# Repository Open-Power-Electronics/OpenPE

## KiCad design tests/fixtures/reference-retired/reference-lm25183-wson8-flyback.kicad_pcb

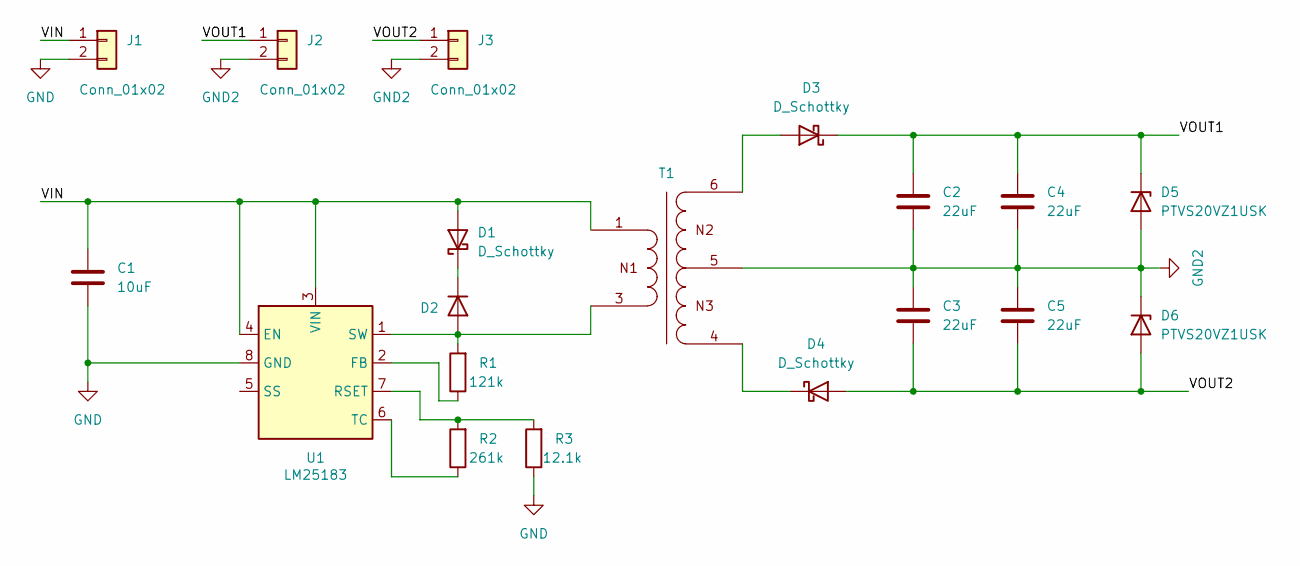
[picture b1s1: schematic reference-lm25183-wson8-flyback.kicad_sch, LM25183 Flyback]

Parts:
C1: 10uF; C_1210_3225Metric
C2, C3, C4, C5: 22uF; C_1210_3225Metric
D1: D_Schottky; D_SMA
D2: D_SOD-123F
D3, D4: D_Schottky; D_PowerDI-123
D5, D6: PTVS20VZ1USK; Nexperia_CFP3_SOD-123W
J1, J2, J3: Conn_01x02; PhoenixContact_GMSTBA_2,5_2-G-7,62_1x02_P7.62mm_Horizontal
R1: 121k; R_0402_1005Metric
R2: 261k; R_0402_1005Metric
R3: 12.1k; R_0402_1005Metric
T1: EP7_5801_750344600; T_Wurth_WE-FLYTI-EP7_5801; Part Number 750344600
U1: LM25183; WSON-8-1EP_4x4mm_P0.8mm_EP2.2x3mm

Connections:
/VIN: C1.1, D1.2 (A), J1.1, T1.1, U1.3 (VIN), U1.4 (EN)
/VOUT1: C2.1, C4.1, D3.1 (K), D5.1 (K), J2.1
/VOUT2: C3.2, C5.2, D4.2 (A), D6.2 (A), J3.1
GND: C1.2, J1.2, R3.1, U1.8 (GND)
GND2: C2.2, C3.1, C4.2, C5.1, D5.2 (A), D6.1 (K), J2.2, J3.2, T1.5
unnamed: D1.1 (K), D2.1 (K)
unnamed: D2.2 (A), R1.2, T1.3, U1.1 (SW)
unnamed: D3.2 (A), T1.6
unnamed: D4.1 (K), T1.4
unnamed: R1.1, U1.2 (FB)
unnamed: R2.2, R3.2, U1.7 (RSET)
unnamed: R2.1, U1.6 (TC)

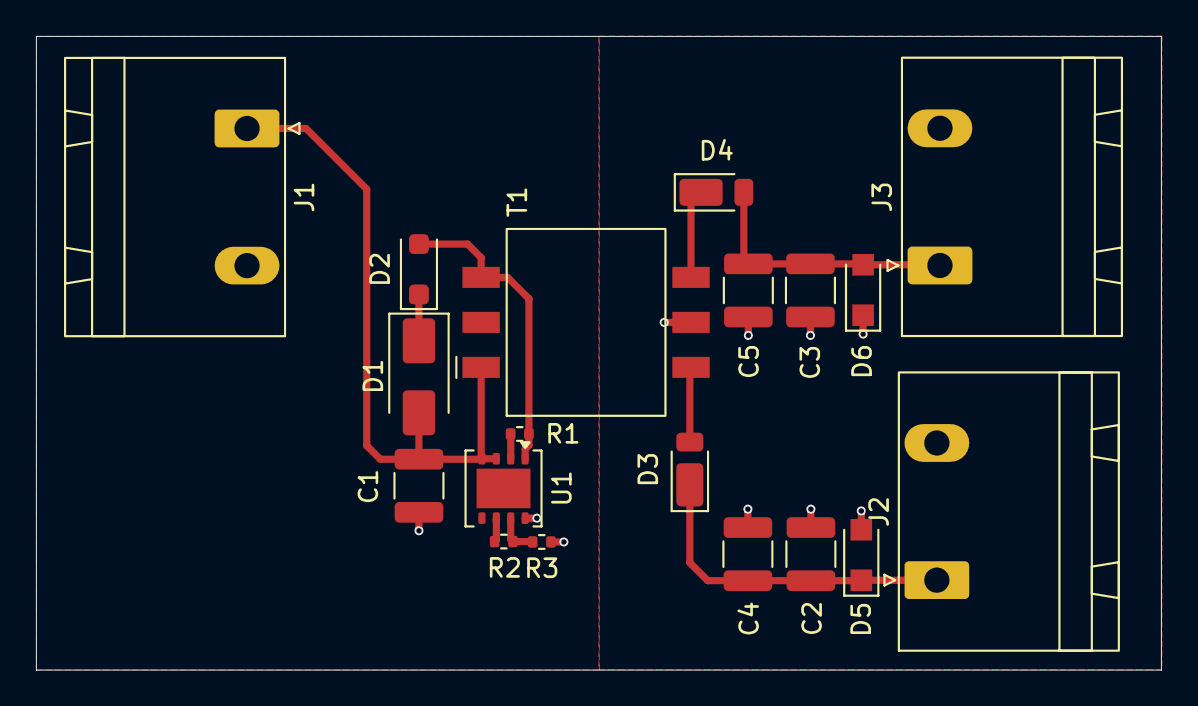
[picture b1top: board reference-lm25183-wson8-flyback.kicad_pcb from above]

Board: 2 copper layers, 62.5 x 35.2 mm, 19 parts (0 on the bottom side), 12 nets.

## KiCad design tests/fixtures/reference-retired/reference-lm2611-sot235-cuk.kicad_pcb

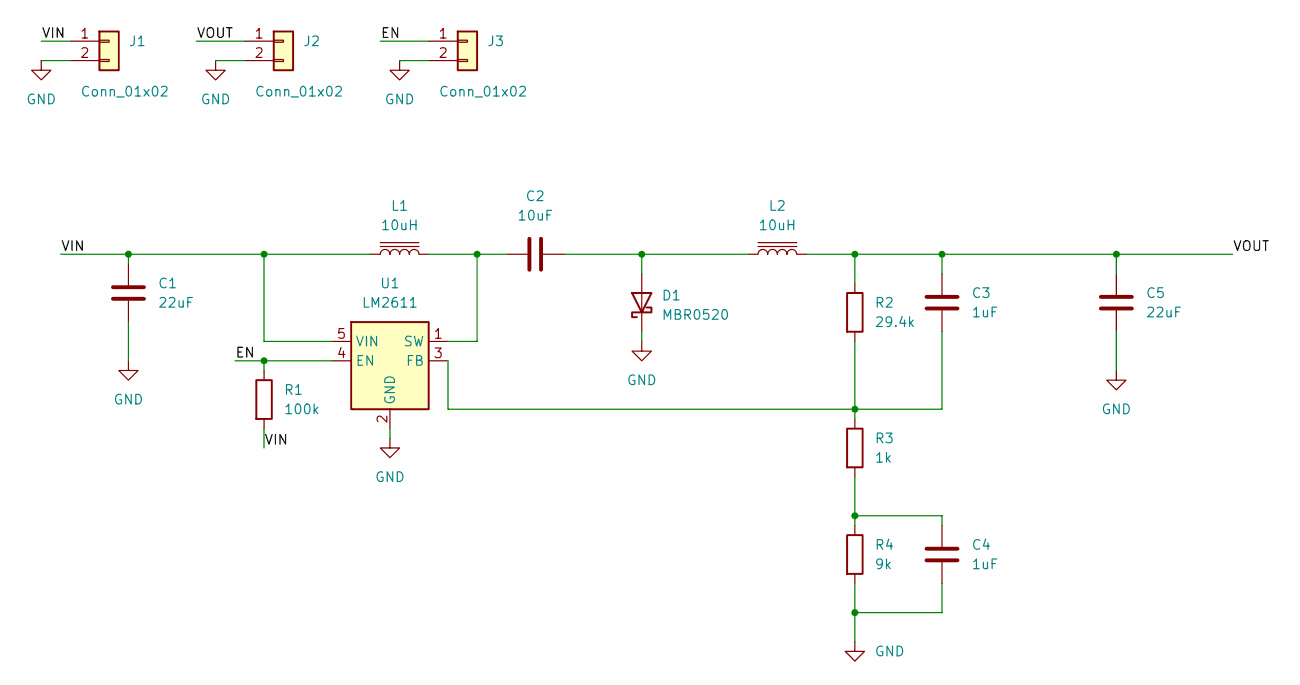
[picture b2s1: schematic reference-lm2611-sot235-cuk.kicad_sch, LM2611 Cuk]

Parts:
C1, C5: 22uF; C_1210_3225Metric
C2: 10uF; C_0603_1608Metric
C3, C4: 1uF; C_0603_1608Metric
D1: MBR0520; D_SOD-123
J1, J2: Conn_01x02; Molex_KK-254_AE-6410-02A_1x02_P2.54mm_Vertical
J3: Conn_01x02; PinHeader_1x02_P1.00mm_Vertical
L1, L2: 10uH; L_Changjiang_FNR6028S
R1: 100k; R_0805_2012Metric
R2: 29.4k; R_0805_2012Metric
R3: 1k; R_0805_2012Metric
R4: 9k; R_0805_2012Metric
U1: LM2611; SOT-23-5

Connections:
/EN: J3.1, R1.1, U1.4 (EN)
/VIN: C1.1, J1.1, L1.1, R1.2, U1.5 (VIN)
/VOUT: C3.2, C5.1, J2.1, L2.2, R2.1
GND: C1.2, C4.1, C5.2, D1.1 (K), J1.2, J2.2, J3.2, R4.2, U1.2 (GND)
unnamed: C4.2, R3.2, R4.1
unnamed: C2.1, D1.2 (A), L2.1
unnamed: C3.1, R2.2, R3.1, U1.3 (FB)
unnamed: C2.2, L1.2, U1.1 (SW)

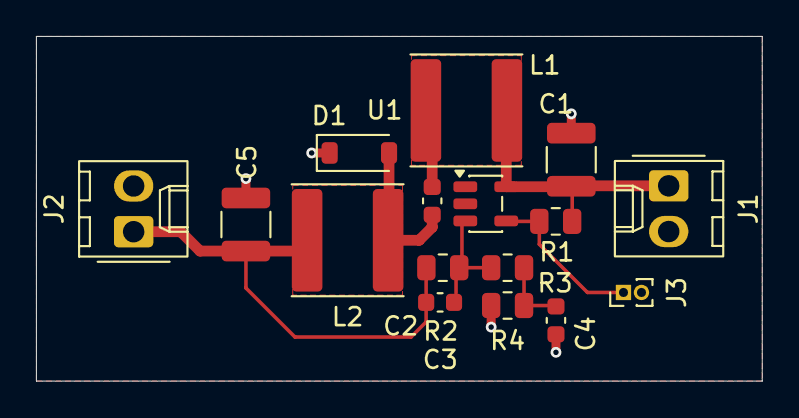
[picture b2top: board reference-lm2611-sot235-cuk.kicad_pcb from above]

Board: 2 copper layers, 40.3 x 19.1 mm, 16 parts (0 on the bottom side), 8 nets.

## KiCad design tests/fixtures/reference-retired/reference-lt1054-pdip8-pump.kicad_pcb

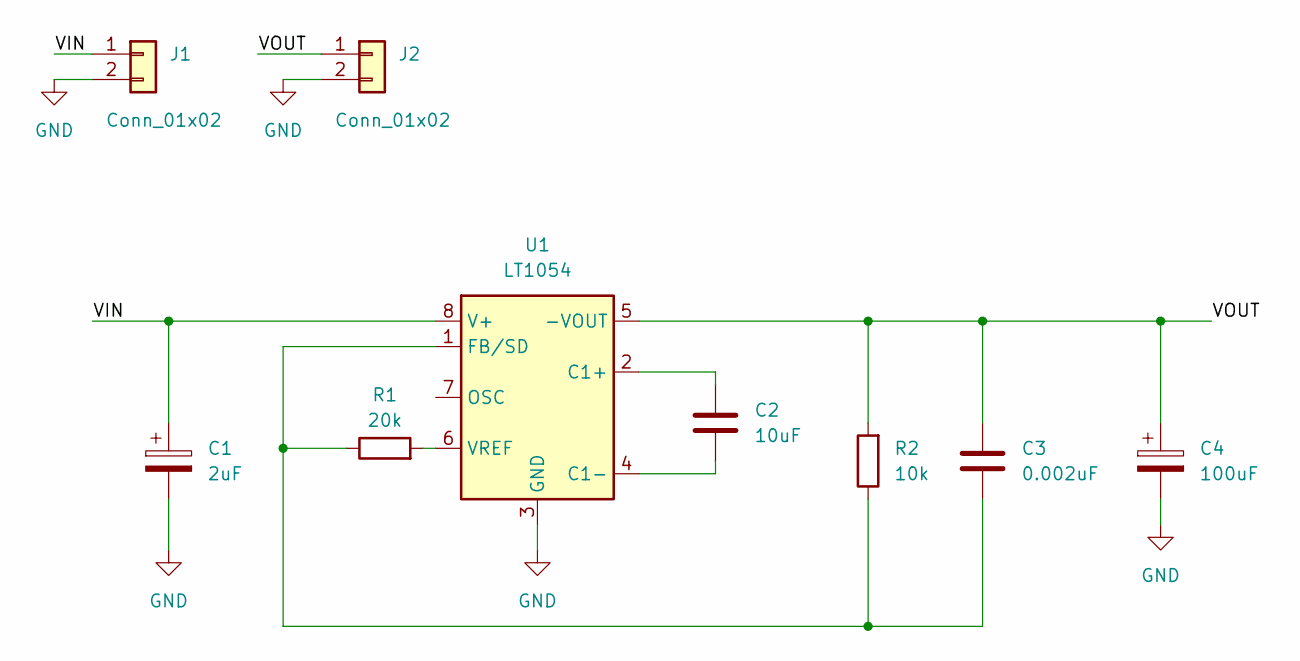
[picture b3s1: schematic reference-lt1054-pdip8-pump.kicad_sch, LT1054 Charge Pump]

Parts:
C1: 2uF; CP_Radial_D6.3mm_P2.50mm
C2: 10uF; C_1210_3225Metric
C3: 0.002uF; C_1210_3225Metric
C4: 100uF; CP_Radial_D6.3mm_P2.50mm
J1, J2: Conn_01x02; JST_PH_B2B-PH-K_1x02_P2.00mm_Vertical
R1: 20k; R_1206_3216Metric
R2: 10k; R_1206_3216Metric
U1: LT1054; DIP-8_W7.62mm

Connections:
/VIN: C1.1, J1.1, U1.8 (V+)
/VOUT: C3.1, C4.1, J2.1, R2.2, U1.5 (-VOUT)
GND: C1.2, C4.2, J1.2, J2.2, U1.3 (GND)
unnamed: C2.1, U1.2 (C1+)
unnamed: C2.2, U1.4 (C1-)
unnamed: C3.2, R1.1, R2.1, U1.1 (FB/SD)
unnamed: R1.2, U1.6 (VREF)

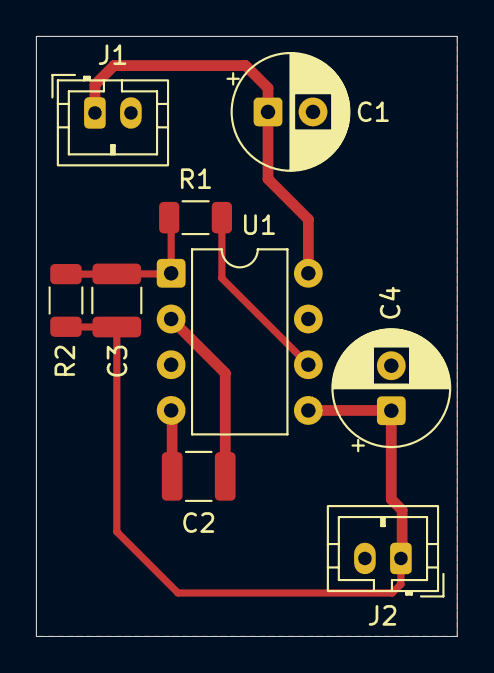
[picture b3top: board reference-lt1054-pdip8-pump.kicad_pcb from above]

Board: 2 copper layers, 23.4 x 33.3 mm, 9 parts (0 on the bottom side), 7 nets.

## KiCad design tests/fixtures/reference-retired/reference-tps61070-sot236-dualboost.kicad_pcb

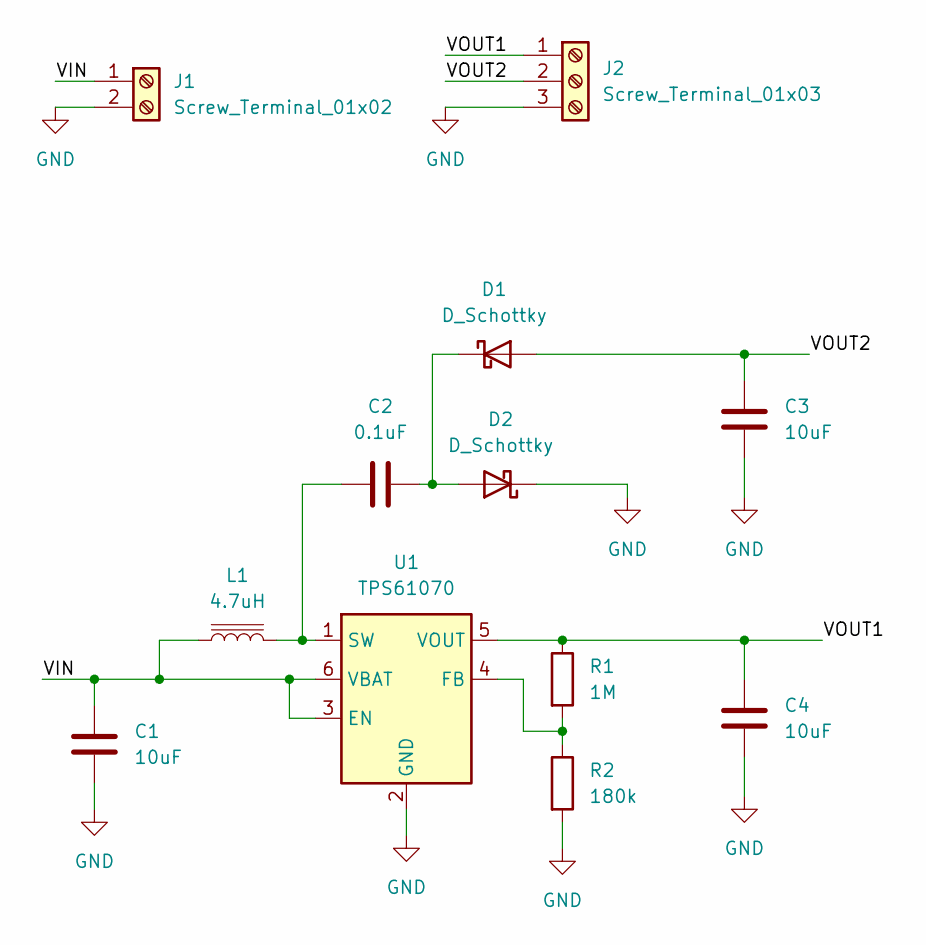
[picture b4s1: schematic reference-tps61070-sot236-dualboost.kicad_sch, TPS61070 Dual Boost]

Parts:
C1, C3, C4: 10uF; C_0805_2012Metric
C2: 0.1uF; C_0805_2012Metric
D1, D2: D_Schottky; D_SOD-123
J1: Screw_Terminal_01x02; TerminalBlock_Phoenix_MPT-0,5-2-2.54_1x02_P2.54mm_Horizontal
J2: Screw_Terminal_01x03; TerminalBlock_Phoenix_MPT-0,5-3-2.54_1x03_P2.54mm_Horizontal
L1: 4.7uH; L_APV_ANR4010
R1: 1M; R_0603_1608Metric
R2: 180k; R_0603_1608Metric
U1: TPS61070; SOT-23-6

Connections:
/VIN: C1.1, J1.1, L1.1, U1.3 (EN), U1.6 (VBAT)
/VOUT1: C4.1, J2.1, R1.1, U1.5 (VOUT)
/VOUT2: C3.2, D1.2 (A), J2.2
GND: C1.2, C3.1, C4.2, D2.1 (K), J1.2, J2.3, R2.2, U1.2 (GND)
unnamed: C2.1, D1.1 (K), D2.2 (A)
unnamed: R1.2, R2.1, U1.4 (FB)
unnamed: C2.2, L1.2, U1.1 (SW)

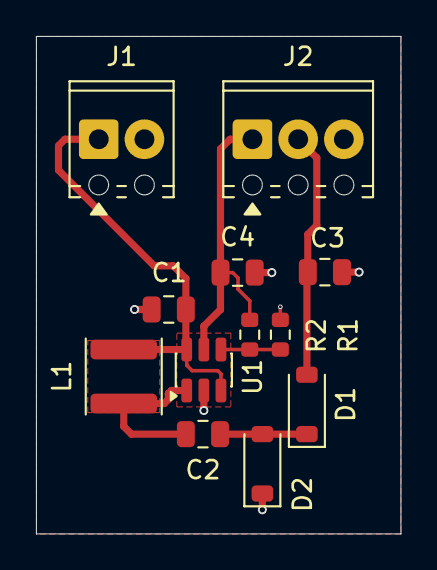
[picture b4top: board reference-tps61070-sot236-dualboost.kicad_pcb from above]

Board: 2 copper layers, 20.2 x 27.6 mm, 12 parts (0 on the bottom side), 7 nets.

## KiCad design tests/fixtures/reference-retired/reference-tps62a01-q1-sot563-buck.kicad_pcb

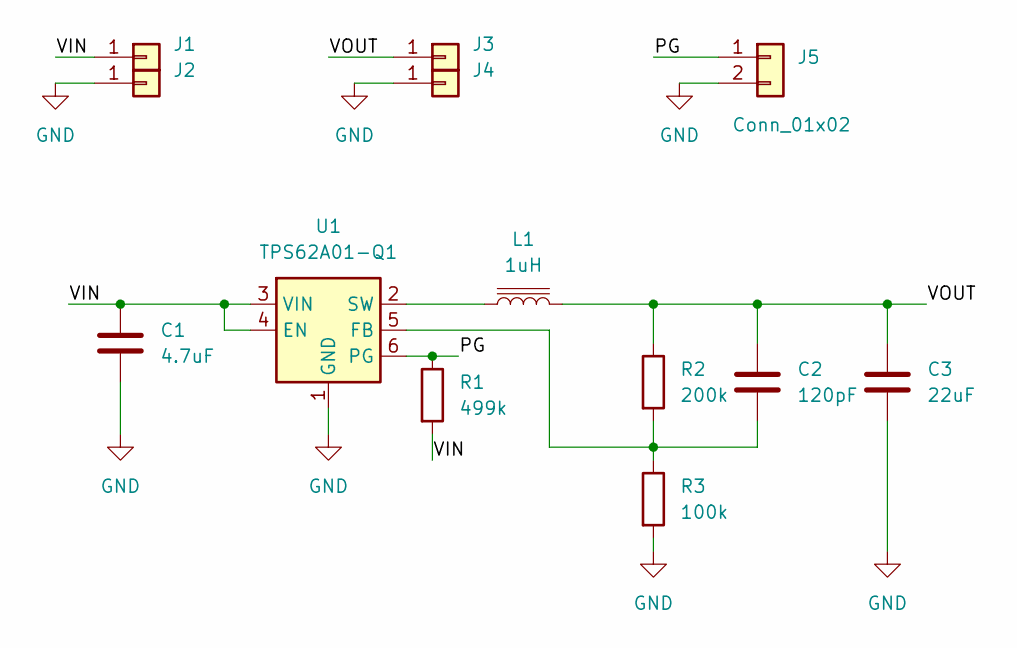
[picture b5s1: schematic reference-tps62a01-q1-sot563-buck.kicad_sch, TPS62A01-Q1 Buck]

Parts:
C1: 4.7uF; C_0805_2012Metric
C2: 120pF; C_0603_1608Metric
C3: 22uF; C_0805_2012Metric
J1, J2, J3, J4: Conn_01x01; SolderWire-0.5sqmm_1x01_D0.9mm_OD2.3mm
J5: Conn_01x02; PinHeader_1x02_P1.27mm_Vertical
L1: 1uH; L_Wurth_WE-LQSH-2512
R1: 499k; R_0603_1608Metric
R2: 200k; R_0603_1608Metric
R3: 100k; R_0603_1608Metric
U1: TPS62A01-Q1; SOT-563

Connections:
/PG: J5.1, R1.1, U1.6 (PG)
/VIN: C1.1, J1.1, R1.2, U1.3 (VIN), U1.4 (EN)
/VOUT: C2.1, C3.1, J3.1, L1.2, R2.1
GND: C1.2, C3.2, J2.1, J4.1, J5.2, R3.2, U1.1 (GND)
unnamed: C2.2, R2.2, R3.1, U1.5 (FB)
unnamed: L1.1, U1.2 (SW)

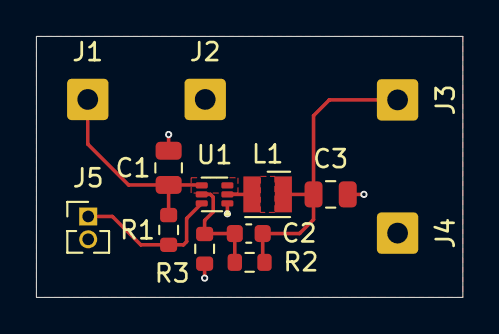
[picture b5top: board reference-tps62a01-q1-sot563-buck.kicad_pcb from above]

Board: 2 copper layers, 23.7 x 14.5 mm, 13 parts (0 on the bottom side), 6 nets.

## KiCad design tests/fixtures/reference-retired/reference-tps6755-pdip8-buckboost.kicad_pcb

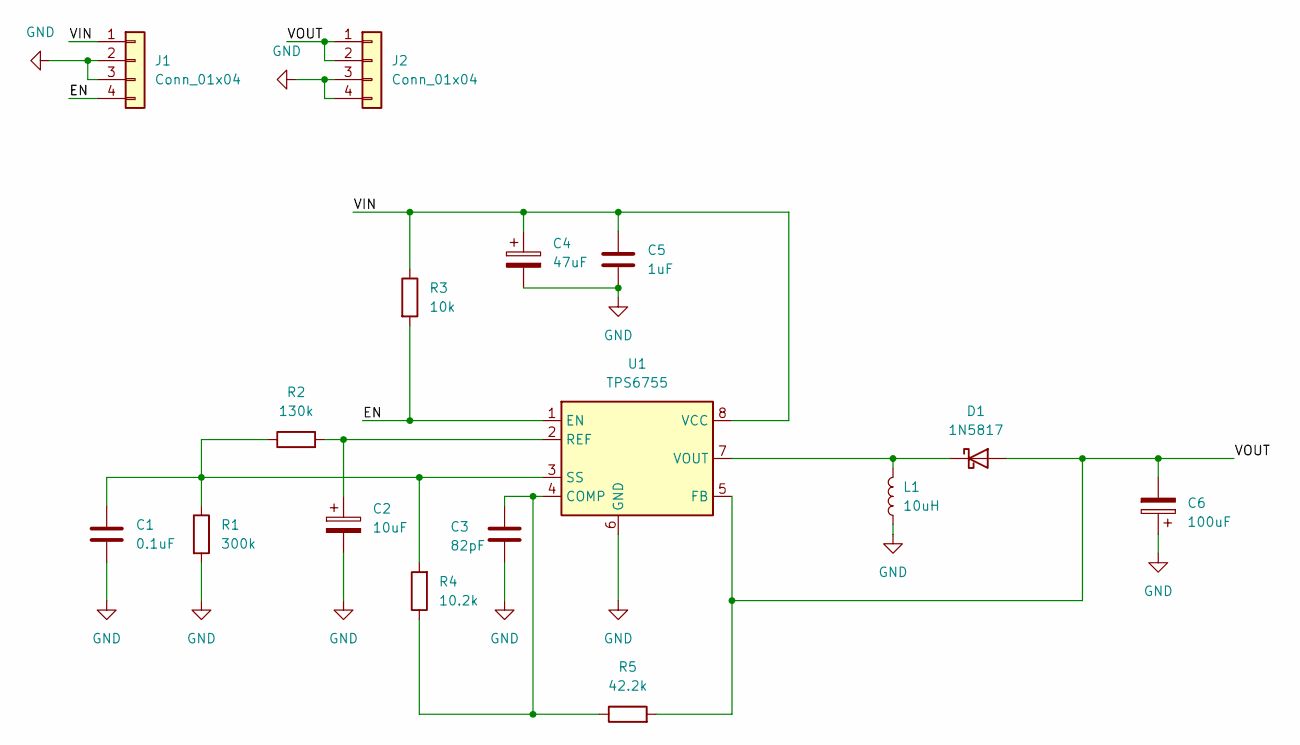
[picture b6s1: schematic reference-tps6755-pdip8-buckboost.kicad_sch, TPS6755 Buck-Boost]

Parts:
C1: 0.1uF; C_0805_2012Metric
C2: 10uF; CP_EIA-3528-12_Kemet-T
C3: 82pF; C_0805_2012Metric
C4: 47uF; CP_EIA-7343-20_Kemet-V
C5: 1uF; C_1206_3216Metric
C6: 100uF; CP_EIA-7343-20_Kemet-V
D1: 1N5817; D_DO-41_SOD81_P10.16mm_Horizontal
J1, J2: Conn_01x04; JST_PH_S4B-PH-K_1x04_P2.00mm_Horizontal
L1: 10uH; L_Changjiang_FXL0640
R1: 300k; R_0805_2012Metric
R2: 130k; R_0805_2012Metric
R3: 10k; R_0805_2012Metric
R4: 10.2k; R_0805_2012Metric
R5: 42.2k; R_0805_2012Metric
U1: TPS6755; DIP-8_W7.62mm

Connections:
/EN: J1.4, R3.2, U1.1 (EN)
/VIN: C4.1, C5.1, J1.1, R3.1, U1.8 (VCC)
/VOUT: C6.2, D1.2 (A), J2.1, J2.2, R5.2, U1.5 (FB)
GND: C1.2, C2.2, C3.2, C4.2, C5.2, C6.1, J1.2, J1.3, J2.3, J2.4, L1.1, R1.2, U1.6 (GND)
unnamed: D1.1 (K), L1.2, U1.7 (VOUT)
unnamed: C3.1, R4.1, R5.1, U1.4 (COMP)
unnamed: C2.1, R2.2, U1.2 (REF)
unnamed: C1.1, R1.1, R2.1, R4.2, U1.3 (SS)

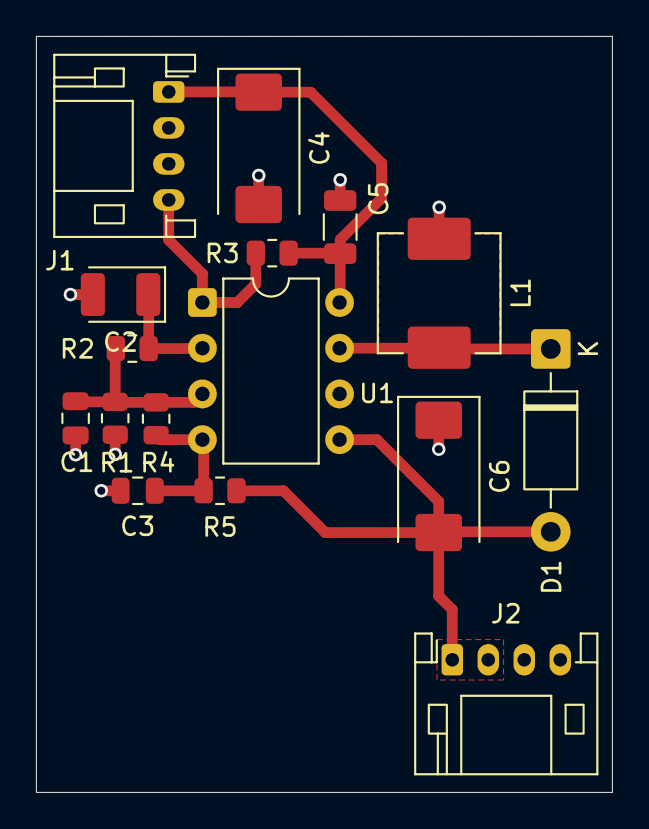
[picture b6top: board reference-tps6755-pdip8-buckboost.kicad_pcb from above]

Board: 2 copper layers, 32.0 x 42.0 mm, 16 parts (0 on the bottom side), 8 nets.
